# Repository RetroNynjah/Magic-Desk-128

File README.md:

# Magic Desk 128 (1MB)

<br/>
This is a Commodore 128 version of the popular Commodore 64 Magic Desk cartridge.
The Magic Desk cartridge is a simple bank switching ROM cartridge that uses IO1 ($de00) to select ROM banks. The difference between this C128 Magic Desk format and the C64 version is that the C128 version has 16kB ROM per bank instead of 8kB and therefore supports twice as much ROM. Theoretically it would support up to 4MB (256x16kB).  
This is the first version of the C128 Magic Desk cartridge and it has room for up to 1MB of ROM divided into 64 banks of 16kB.

The cartridge was designed with SST39 flash chips in mind but other 32-pin flash or EPROM/EEPROM chips can be used too as long as they are pin-compatible.

### Startup
After power-up or reset, ROM bank 0 (the first 16kB of the LOW chip) is active and accessible at $8000-$bfff.  
That first bank needs to contain the regular cartridge initiation bytes such as CBM magic word, autostart configuration and start vectors if you want your cartridge to autostart.

### Switching banks
Write an address of a ROM bank such as #00-#63 (#$00-#$3f in hex) to $de00 to switch bank. Set the value to 63 to switch to the last bank of the second ROM and value 0 to switch back to the first bank in first ROM or any bank in between.
The size and amount of ROM chips is flexible. It's even possible to mix and match chips of different sizes to match your needs but you need to be aware of the available bank numbers when doing so.
The LOW chip contains banks 0-31 and the HIGH chip contains 32-63. 
It doesn't make sense to add a HIGH chip if there's anything less than a 4Mbit/512kB (SST39SF040) chip in the LOW position but it is possible. You just have to skip some of the banks from the LOW range and skip to bank 32 to read from the HIGH chip.

### Precautions
ROM banks are switched whenever IO1 is asserted which is when any address between $de00 and $deff is accessed.
Writing to any of these addresses will switch the bank the same way as $de00 does.
Reading from any adress between $de00 and $deff corrupts the bank selection by switching bank to a somewhat random bank so if you for some reason would like to read from these addresses in your application you must make a proper bank selection afterwards.
I don't know of any program that reads from that area but if a program does that it can't be used on a multicart created with the Magic Cartridge Generator if you don't modify the program.

## ROM population examples
|LOW chip   |HIGH chip	|Banks      |Total size |
|----------	|----------	|-----	    |----------	|
|SST39SF010	|           |0-7        |128kB      |
|SST39SF010	|SST39SF010	|0-7, 32-39 |256kB		|
|SST39SF020	|           |0-15		|256kB	  	|
|SST39SF040	|           |0 -31      |512kB      |
|SST39SF040	|SST39SF020	|0-47		|768kB		|
|SST39SF040	|SST39SF040	|0-63		|1024kB	  	|

If you use a smaller chip such as the SST39SF010, the data in the eight available banks will be repated at bank address 8-15, 16-23, 24-31.

## BOM
|identifier |Part                 |Comments                         |
|----------	|----------	          |-----							|
|U1         |74LS273              |or 74HCT273/74AHCT273            |
|U1         |74LS02               |or 74HCT02/74AHCT02              |
|U3         |32-pin flash/EPROM   |First ROM. SST39SF or compatible |
|U4         |32-pin flash/EPROM   |Second ROM (optional)            |
|C1,C2,C3,C4|100nF ceramic        |5mm pitch                        |

## Software
### Volley for Two
The game Volley for Two is the reason that I developed this cartridge format in the first place. I started working on the cartrige when the programmer Jonas Hultén wanted a cartridge format to release the game on. He modified the game to load from a Magic Desk 128 cartridge.

You can download cartridge ROM file along with printable labels and more from https://kollektivet.nu/v42/  
The game needs a 256kB (SST39SF020) or larger flash chip.

### Magic Cartridge Generator
Zzarko has made a Python script and a menu program that can be used to generate menu-driven multi-cart images that can be put on this cartridge.  
Create a cartridge with all your favorite C128 utils or games. The requirement is that they consist of a single prg-file (no multi-load programs). 
Zzarko's Magic Cartridge Generator along with documentation and examples can be found at https://bitbucket.org/zzarko/magic-cartridge-generator

### Emulator Support
The Kernal64 emulator can emulate this cartridge.
At the moment you will have to mount the ROM image from the internal function ROM configuration and set the type to MAGICDESK128.  
The Kernal64 project can be found at https://github.com/abbruzze/kernal64

VICE supports emulation of the Magic Desk 128 from version 3.7.  
Mounting a regular bin file can be done by starting Vice with the command line parameter *-cartmd128 <romfile.bin>*  
Cartridge images in crt format can be opened using the attach cartridge function in the menu. The crt files can be generated from bin files using version 3.7 or newer of the command cartconv using the below syntax.  
```cartconv -t md128 -i romfile.bin -o cartfile.crt -n "Your display name"```

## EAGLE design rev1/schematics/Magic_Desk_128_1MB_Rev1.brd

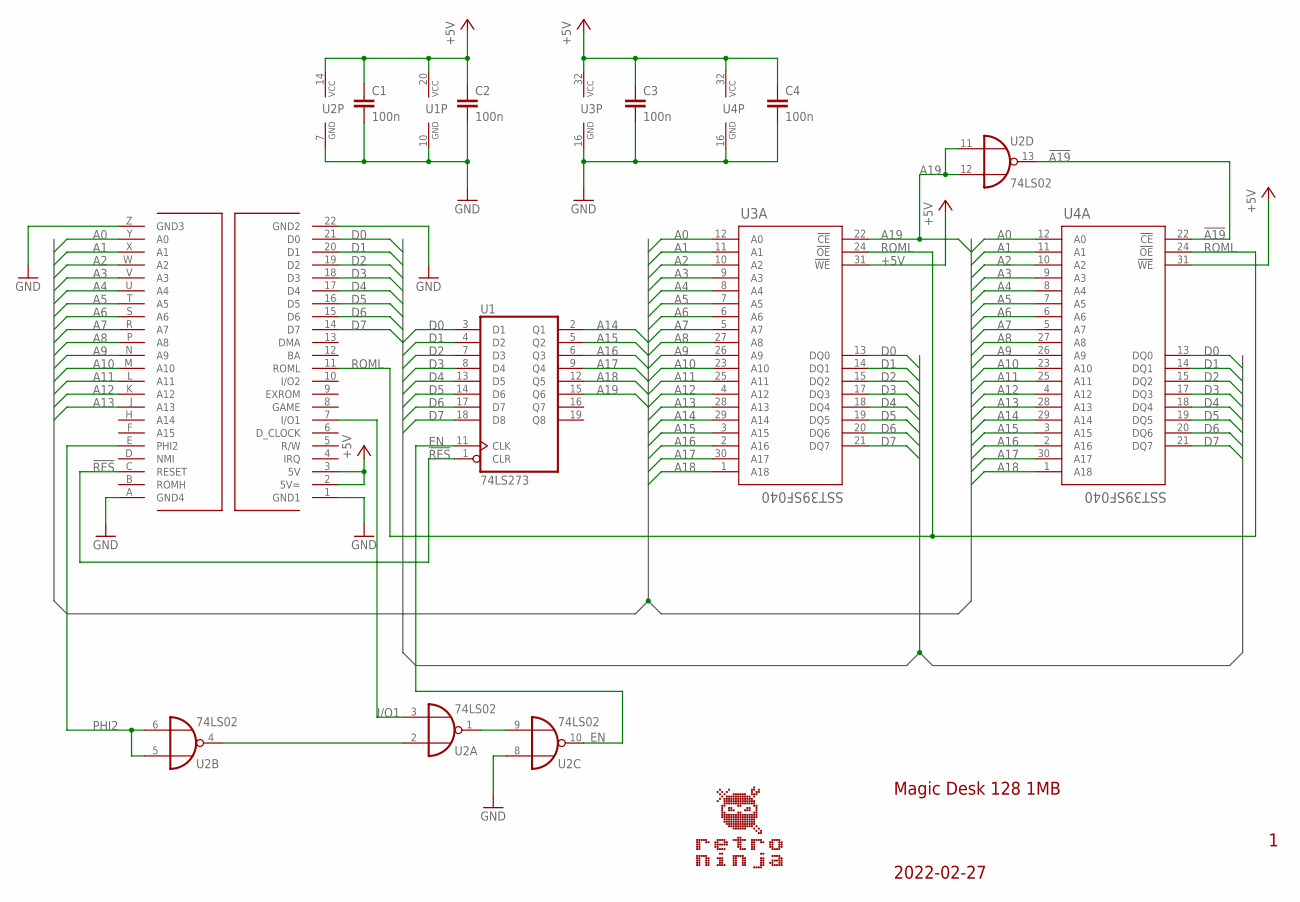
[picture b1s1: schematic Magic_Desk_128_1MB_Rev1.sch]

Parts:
C1, C2, C3, C4: 100n; CAP_5MM_2.5X5.0_ROUND
CN1: C64_CARTRIDGE_PORT_CARTEDGE; C64_CARTRIDGE_BOARDEDGE
U1: 74LS273; DIL20
U2: 74LS02; DIL14
U3, U4: SST39SF040; DIL32-6

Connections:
!A19: U2.13 (O), U4.22 (!CE)
!RES: CN1.C (RESET), U1.1 (CLR)
+5V: C1.1, C2.1, C3.1, C4.1, CN1.2 (5V=), CN1.3 (5V), U1.20 (VCC), U2.14 (VCC), U3.31 (!WE), U3.32 (VCC), U4.31 (!WE), U4.32 (VCC)
A0: CN1.Y (A0), U3.12 (A0), U4.12 (A0)
A1: CN1.X (A1), U3.11 (A1), U4.11 (A1)
A2: CN1.W (A2), U3.10 (A2), U4.10 (A2)
A3: CN1.V (A3), U3.9 (A3), U4.9 (A3)
A4: CN1.U (A4), U3.8 (A4), U4.8 (A4)
A5: CN1.T (A5), U3.7 (A5), U4.7 (A5)
A6: CN1.S (A6), U3.6 (A6), U4.6 (A6)
A7: CN1.R (A7), U3.5 (A7), U4.5 (A7)
A8: CN1.P (A8), U3.27 (A8), U4.27 (A8)
A9: CN1.N (A9), U3.26 (A9), U4.26 (A9)
A10: CN1.M (A10), U3.23 (A10), U4.23 (A10)
A11: CN1.L (A11), U3.25 (A11), U4.25 (A11)
A12: CN1.K (A12), U3.4 (A12), U4.4 (A12)
A13: CN1.J (A13), U3.28 (A13), U4.28 (A13)
A14: U1.2 (Q1), U3.29 (A14), U4.29 (A14)
A15: U1.5 (Q2), U3.3 (A15), U4.3 (A15)
A16: U1.6 (Q3), U3.2 (A16), U4.2 (A16)
A17: U1.9 (Q4), U3.30 (A17), U4.30 (A17)
A18: U1.12 (Q5), U3.1 (A18), U4.1 (A18)
A19: U1.15 (Q6), U2.11 (I0), U2.12 (I1), U3.22 (!CE)
D0: CN1.21 (D0), U1.3 (D1), U3.13 (DQ0), U4.13 (DQ0)
D1: CN1.20 (D1), U1.4 (D2), U3.14 (DQ1), U4.14 (DQ1)
D2: CN1.19 (D2), U1.7 (D3), U3.15 (DQ2), U4.15 (DQ2)
D3: CN1.18 (D3), U1.8 (D4), U3.17 (DQ3), U4.17 (DQ3)
D4: CN1.17 (D4), U1.13 (D5), U3.18 (DQ4), U4.18 (DQ4)
D5: CN1.16 (D5), U1.14 (D6), U3.19 (DQ5), U4.19 (DQ5)
D6: CN1.15 (D6), U1.17 (D7), U3.20 (DQ6), U4.20 (DQ6)
D7: CN1.14 (D7), U1.18 (D8), U3.21 (DQ7), U4.21 (DQ7)
EN: U1.11 (CLK), U2.10 (O)
GND: C1.2, C2.2, C3.2, C4.2, CN1.1 (GND1), CN1.22 (GND2), CN1.A (GND4), CN1.Z (GND3), U1.10 (GND), U2.7 (GND), U2.8 (I0), U3.16 (GND), U4.16 (GND)
I/O1: CN1.7 (I/O1), U2.3 (I1)
unnamed: U2.2 (I0), U2.4 (O)
unnamed: U2.1 (O), U2.9 (I1)
PHI2: CN1.E (PHI2), U2.5 (I0), U2.6 (I1)
ROML: CN1.11 (ROML), U3.24 (!OE), U4.24 (!OE)

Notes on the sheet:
2022-02-27
Magic Desk 128 1MB

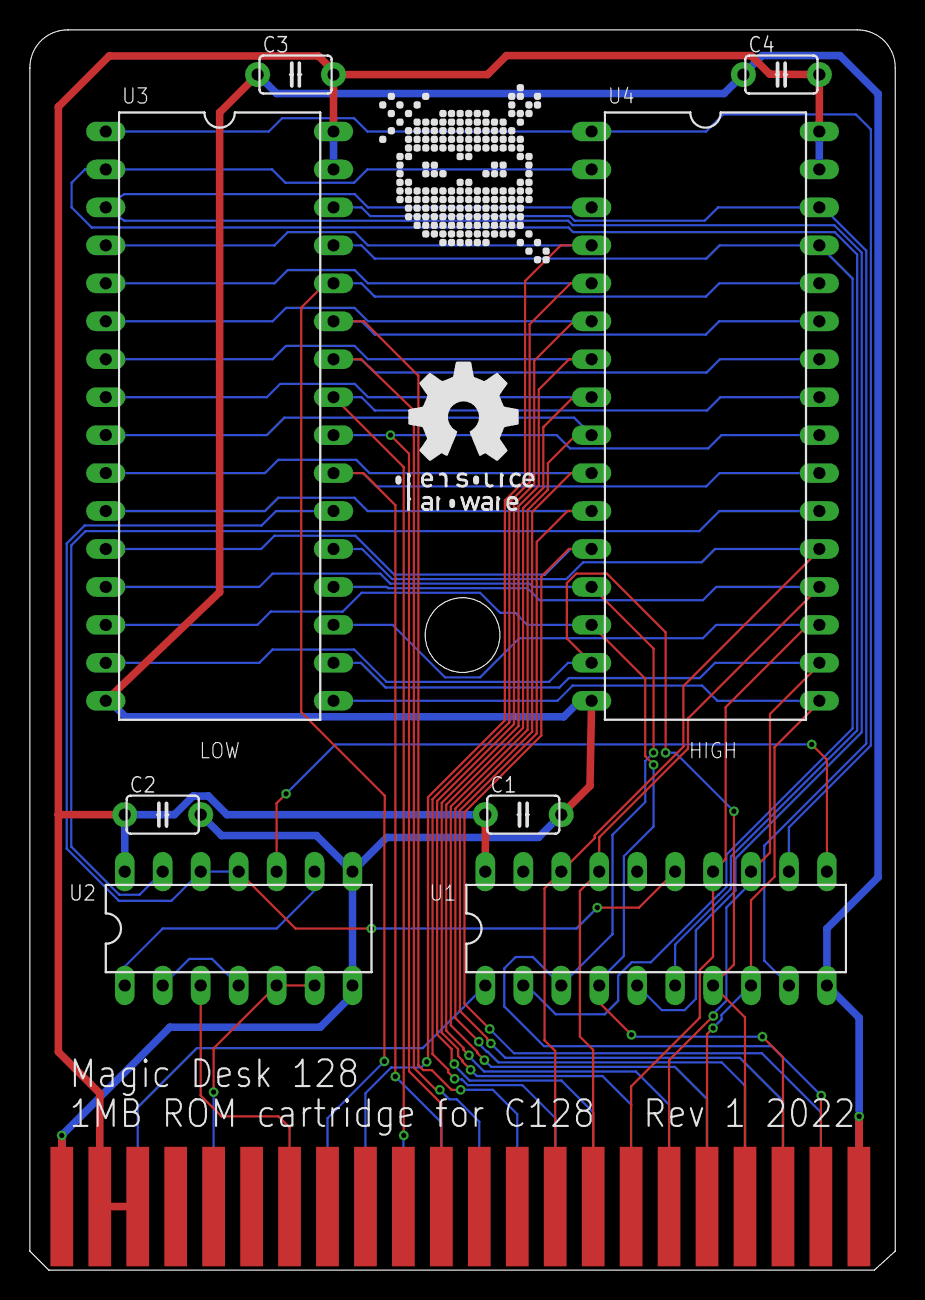
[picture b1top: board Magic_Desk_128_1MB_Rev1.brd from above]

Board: 2 copper layers, 57.9 x 83.0 mm, 11 parts (0 on the bottom side), 38 nets.

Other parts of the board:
U$1: RETRONINJA_NOTEXT_12MM
U$2: OSHW_10MM

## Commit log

2022-03-06 Upload
2022-04-11 Update README.md
    Magic Cartridge Generator
2022-06-16 Update README.md
    Corrected bank numbers in addressing example
2022-06-16 Update README.md
    Corrected addressing example
2022-06-29 Update README.md
    Link to Volley for Two
2022-09-27 Update README.md
    Supported in Kernal64 emulator
2022-09-30 Update README.md
    Vice emulator support
2022-10-01 Update README.md
    Corrected (removed) information about ROMH area.
    Added a precations section about reading from $de00-$deff
2023-01-15 Update README.md
    Vice 3.7 and cartconv information
